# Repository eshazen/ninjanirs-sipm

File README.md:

# ninjanirs-sipm

Power supplies and electronics for SiPM-based optodes

Designs completed:

*  `KiCAD/lt3014-test` - test board with LT3014 voltage regulator
controlled by AD5270 digital pot, with INA201 current limiter
   * See [README](Testing/LT3014/README.md) for test details
* `KiCAD/sipm-hv-splitter` - candidate for in-system test
   * See [README](KiCAD/sipm-hv-splitter/README.md) for testing

Test logs:

* `Testing/LT3014` for the test board
* `Testing/sipm-splitter` for the splitter board

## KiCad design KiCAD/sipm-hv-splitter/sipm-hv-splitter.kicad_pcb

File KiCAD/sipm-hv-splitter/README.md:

# sipm-hv-splitter

## Description

This is a PCB intended to replace the "splitter" board, connecting
directly to a detector interface card with a very short ribbon.
It provides programmable, current-limited HV bias to 8 SiPMs along
with TIA readout of each SiPM.

The targent dimensions for the prototype are 2.5 x 1.3 inches.

The SiPM connectors are the "NIRX" standard .050" pitch 4-pin with
pinout as follows (top view of female header on this board):

| Function   | Number |   | Number | Function     |
|------------|--------|---|--------|--------------|
| V(BIAS)    | 2      |   | 1      | Signal       |
| Thermistor | 4      |   | 3      | GND (shield) |

The thermistor is optional and expected to be connected on only 1 of 8
SiPMs. 

The output connector to the readout adapter has the following pinout:

| Function | Number |   | Number | Function    |
|----------|--------|---|--------|-------------|
| V +12V   | 1      |   | 2      | V -20V      |
| GND      | 3      |   | 4      | Ch 7 signal |
| V +12V   | 5      |   | 6      | V -20V      |
| GND      | 7      |   | 8      | Ch 6 signal |
| V +12V   | 9      |   | 10     | V -20V      |
| GND      | 11     |   | 12     | Ch 6 signal |
| V +12V   | 13     |   | 14     | V -20V      |
| GND      | 15     |   | 16     | Ch 4 signal |
| V +12V   | 17     |   | 18     | V -20V      |
| GND      | 19     |   | 20     | Ch 3 signal |
| V +12V   | 21     |   | 22     | V -20V      |
| GND      | 23     |   | 24     | Ch 2 signal |
| V +12V   | 25     |   | 26     | V -20V      |
| GND      | 27     |   | 28     | Ch 1 signal |
| V +12V   | 29     |   | 30     | V -20V      |
| GND      | 31     |   | 32     | Ch 0 signal |
| COMM/RX  | 33     |   | 34     | COMM/RX     |

_NOTE:_ channel number order reversed to minimise crosstalk on the PCB.

`COMM/RX` is a logic signal (optionally containing UART prototcol
data) from the adapter card to the on-board MCU.  `COMM/TX` is an
optional half-duplex return path for bidirectional communication with
the adapter card.

## ECOs

* Cut track to SDO U5 pin 7 at chip.  Add 2.2k pull-up to 3.3V
on pin 7.
* Cut track to BOOST_ENA and wire to PD5 (pin 9) of U1.
* C39 wrong footprint on schematic/BOM (0201)

## Testing Log

### 11/11/26:

Summary:

Up to about 2.5mA is OK at 56V.  Firmware is updated
to provide more margin for failures.  Currently:

	DAC            195 (56V)
	ADC_VOLT_NOM   779 (55.8V) with range +/-10
	                    55.0 .. 56.6 more or less
    ADC_VOLT_LOW   472 (32V) at minimum VR output
	ADC_CURRENT_LOW 50 (1mA) at minimum VR output

Update board#1 firmware to current (tag `Splitter-FW-V1.1`).
<br>Modify the detector IF card I have bypass U13

--------------------------------------------------
Wire up a NIRx cable to alligator clip adapter.

Test with 47k load in parallel with 75k = 28.9k
<br>57/29.9 = 1.73mA

    > a
    56.8 V 1717.0 uA -104.0 degC
    >a 0
    83

ADJ on U4 is 1.2V

Try 10k (8.8k or 6.5mA).  Output is 62V on meter

    >a
    72.8 V 6723.2 uA -104.0 degC

<br>ADJ is 1.5V!
<br>IMON is ~ 1.1V
<br>Also 350mV 25kHz oscillation at end of NIRx cable.
<br>Pins on U2 (INA201):

    2 - 1.1
    3 - 0.287

    >a
    72.4 V 3599.5 uA -104.0 degC
    >a 0
    171
    >

Measure IMON @ 600mV.  (this is the trip point)

Back to 75k

    >a
    56.8 V 786.1 uA -104.0 degC
    >a 0
    39

Measure IMON @ 126mV.  

Test with 44k = 27.7k or 2mA.

    >a
    56.8 V 1841.1 uA -104.0 degC
    >a 0
    90
    >

With 22k bad news.  U4 VR output is 72V and ADJ=1.5V!

(realize that the SiPM Anode connection is not a good place
to connect my dummy load, so move to the shield (GND)).

Try again with 22k and see the same issue.
<br>44k is OK.
<br>32k (parallel with 75k so 22k) is OK.  Current = 2.5mA.

    >a
    56.8 V 2234.1 uA -104.0 degC
    >a 0
    108

Measure voltages:

    55.6 at testpoint (boost out)
    53.9 at end of cable.  
	
1k series gives a 1.8V drop so that's consistent	

### 11/10/26:

Board#2 is in the hands of Srikanth.  Seems to work OK but trips with
4 optodes exposed to room light.

Preparing Board#1 for shipment to NIRx.  Power up as-is with 12V.
LED D3 comes on briefly, then off.  D2 (trip) then on steady.
If the ISP is connected, D3 blinks fast.

Wire up 75k load on a NIRx cable and connect to optode #1.
Now get trip and fast blink.  Re-flash with debug software.

Power-up sequence:

    >p 170
	>vs 0
	>b 1
    >a
    56.9 V 765.4 uA -104.0 degC
	>a 0
    39

This seems reasonable.  57V / 75k = 760uA.

Recalculate trip point.  INA201 amp gain 50V/V
<br>Comparator VREF = 0.6V
<br>With R2=210k and R3=75k trip at IMON = 2.28V
<br>(2.28V/50)/3 = 15mA

Readback:  IMON = current * 3 Ohms * 50
<br>So 760uA * 3 * 50 = 114mV or 35 ADC counts.

### 2/26/26:

Thinking some more about the observed issues.  On the splitter the delta-v on
the LT3014 output is around 50mV, while on the test board with the MOSFET
load circuit it's more like 20mV.  50mv/57V * 1.2V = 1.1mV on the ADJ pin.
It seems not unlikely that ground bounce or capacitative coupling into the
ADJ pin could cause this.

Interesting... there is a C installed at C15 (soft start).  Try removing it.
Much better.

### 2/3/26:

Change feedback C on ch1 TIA from 1nf to 100pF.
<br>Oscillation gone!

Work plan after chat with BZ:

* Try various FB C's to make sure we're in a good range
* Change all FB C's on working board
* Test for measurable x-talk during 1.25ms pulse on neighboring channel
   * Shift in baseline
   * Change in Vbias
* Test with more SiPMs

<br>Change ch 2 FB to 470pF.  No oscillation.
<br>Change ch 1 FB back to 1000pF.  Yes oscillation (sanity check)
<br>Change ch 1-4 FB to 470pF.

### 2/2/26:

Power-up sequence:

    >p 170
	>vs 0
	>b 1

Should read 57V or so.  Note dummy load needed to avoid trip.

Testing S13360-3025PE.  3x3mm 25um pitch.  Vover = 5V, VBR 53+/-5
<br>Confirm that VBR is about 53.

   S13360-3025PE (gain 7e5)
   pot = 195.  V is 56V, 170uA+/-50uA
   100Hz pulse 100us wide 3.2V into red LED
   Output about 420mV.
   
Printing another box for a 2nd SiPM.

   S13360-3050PE (gain 1.7e6)
   Output about 3.95V
   
Gain should be about 2.5X higher.

__Oscillation:__ See 50MHz sine wave ~ 20mV pk-pk output of amp.
<br>With only open NIRX cable (60cm) we see a square-ish wave almost 100mV pk-pk.

The amp has a low-pass filter with ~10kHz cutoff.
<br>Try 100pF in parallel with the 1nF feedback cap.  If anything, worse.

### 1/22/26:

See below 8/7/25 for power hookups

Test board `OUT0` is pin 4 of ribbon, so SIG_0 which comes from pins 29-32 of Optodes header

Boost converter producing 73V but output always tripped.  Need dummy load?
<br>Make a optode cable with 100k.  Now it works!

The current readback seems wrong, though.  57/100k = 560uA
<br>The readout says 72.6uA

ADC is reading 31.  Sense resistor is 3.00 ohms.  So the raw current signal
should be 1.7mV across R9.  For the INA201 the gain is supposedly 50V/V
so 84mV for 560uA.  The expected ADC reading would be 26.  Observe 31-35
using raw `a 0` so maybe not so bad?

In `sipm_io.h` constant `NA_PER_ADC` is 2200.  Hmm.
Change to 20687.

### 9/30/25:

Testing board#2

* Power-up and flash OK.
* Boost output 73V
* VR range 31.2-60.8

* Change R17 to 2.7M to increase max voltage to 67V

Now the VR goes up to 65.2.

The current readback is jumping around from 8-20uA though.

Re-flash board#1 with avr-debug

Current readback similarly jumps around

### 9/17/25:

(all below board#1)

Finally have correct (hope) ribbon between test board and adapter.
Going to install firmware on the purple test board.

Currently it has:

```
hazen@hazen-botlab CIRCUITPY $ ls -l
total 6
-rw-r--r-- 1 hazen hazen  103 Dec 31  2019 boot_out.txt
-rw-r--r-- 1 hazen hazen 1608 Dec 18  2022 code.py
-rw-r--r-- 1 hazen hazen 2671 Dec 19  2022 DetAdapterTB.py
drwxr-xr-x 2 hazen hazen  512 Dec 31  2019 lib
```

(lib is empty).  Copying the following from BZ's ZIP:

```
-rw-rw-rw- 1 hazen hazen     889 Aug 28 00:51 code.py
-rw-rw-rw- 1 hazen hazen    8512 Aug 28 00:47 NN22DetectorAdapterTestBoard.py
-rw-rw-rw- 1 hazen hazen    3982 Oct 17  2024 TestFunctions.py
```

It works!  SiPM output voltage reported by python on the test board
varies with LED current.

### 9/12/25:

Working towards readout with BZ's red and purple boards.

TODO:

* Install R63, remove R62 on red board.  This disables the on-board LED and repurposes `A_COMM` as an
enable for the HV.  _Done_ (100 ohms for R63)
* Make firmware which powers up the HV and displays status
on the HV board LED.

### 9/11/25:

* Change R13 to 180k to up boost output to 75V.
* Change R17 to 2.7M to increase max voltage to 67V

Confirm with VOM we get 66.5V max output or so.

### 8/27/25:

Looking to use [test board](https://github.com/eshazen/ninjanirs-optode/tree/main/KiCAD/test-board) as a breakout.

```
  +6.5V  -  use for +12V power
  GND    -  ground
  -20V   -  use for -20V for TIA negative power
```

Solder wires to J1 pins 33 (comm TX) and 34 (comm RX).

### 8/20/25:

Load resistor of 66k on outputs.  Script `ramp_plot.py` makes
a nice set of V, I curvs vs DAC setting.

Ripple with scope probe ~ 20mV pk-pk.  100MHz always present,
20Hz (!) only when boost converter on.

Install parts for detector 0:

```
   R44, C47  (1k, 0.1uF) bias filter
   C23, C31 (0.1uF) bypass
   R28 (15k, TI)
   U13 (opa)
   R36 (15 ohms) output
   C39 (1n) feedback
```

### 8/4/25:

Issues with oscillation on output; seems like the LT3014.
Change C11 and C12 to 1uF 100V (vs 0.1uF).  Seems better.
Still some issues with startup.

Change R3 from 140k to 75k (double the overcurrent).
Now all seems good except for some ripple at max output.
Change R13 from 180k to 160k to up boost output to 65V.

All good so far.

### 7/29/25:

Add 2.2k pull-up on Digi Pot SDO.  It works!
<br>Move `BOOST_ENA` to PD5

Install U4, R17, R20 and C11, C12 as 0.1uF 100V.

### 7/28/25:

Started a new board, installed MCU and digi pot.

Found that ISP is unreliable here too.  Cut "SDO" track from digipot.
Now it seems to work reliably.  But Digi pot doesn't work.

Notice that the data sheet says that a pull-up is *required* on SDO
even if not used.

### 7/24/25:

Found a "feature" of the AVR SPI bus:  The pin called nSS (PB2)
must be driven high for the SPI bus to work.  We're using this
for BOOST_ENA so this is a bit of a problem.

More seriously, the ISP interface on the AVR seems to be dead.
This could be because we were using the ISP in 5V mode :(
<br>One can set 3.3V (host power) mode by removing the little yellow jumper
on the USBTinyISP.

May need to solder up a new board :( :(
<br>Start on board#2.  Install only 3.3V digital and MCU.
Programs fine.  Stopping for the weekend.

### 7/23/25:

Soldered 3.3V regulators, MCU and boost converter parts.
Soldered temporary FTDI serial thing on R1 site.

Boost converter works!  Outputting 61.3V, drawing 69mA on 12V.
Controlled as expected by `BOOST_ENA` output from MCU.

Install Digi pot.  Doesn't work :(  <br>
Verified SCK, MOSI, nSYNC all look OK. <br>
Nothing comes out MISO, POT stuck at 50%. <br>

Giving up for today

## Revision log

### 7/7/25:
Final checks

* Add LC filter on AVCC on MCU
* Add filter C on AREF
   * working on layout changes

### 7/3/25:  
First complete draft, posted to Basecamp

### Edits due from BZ on 7/1/25:

* Mis-wired RC filter on TIA input; should be on each SiPM bias line.
<br>_NOTE:_ the RC filter should be moved to the heirarchial block for
each channel for common layout? *DONE*
* Swap UART TX/RX *DONE*
* Use same symbol for all caps C2, C3 etc *DONE*
* Add filter on `THERM` *DONE*

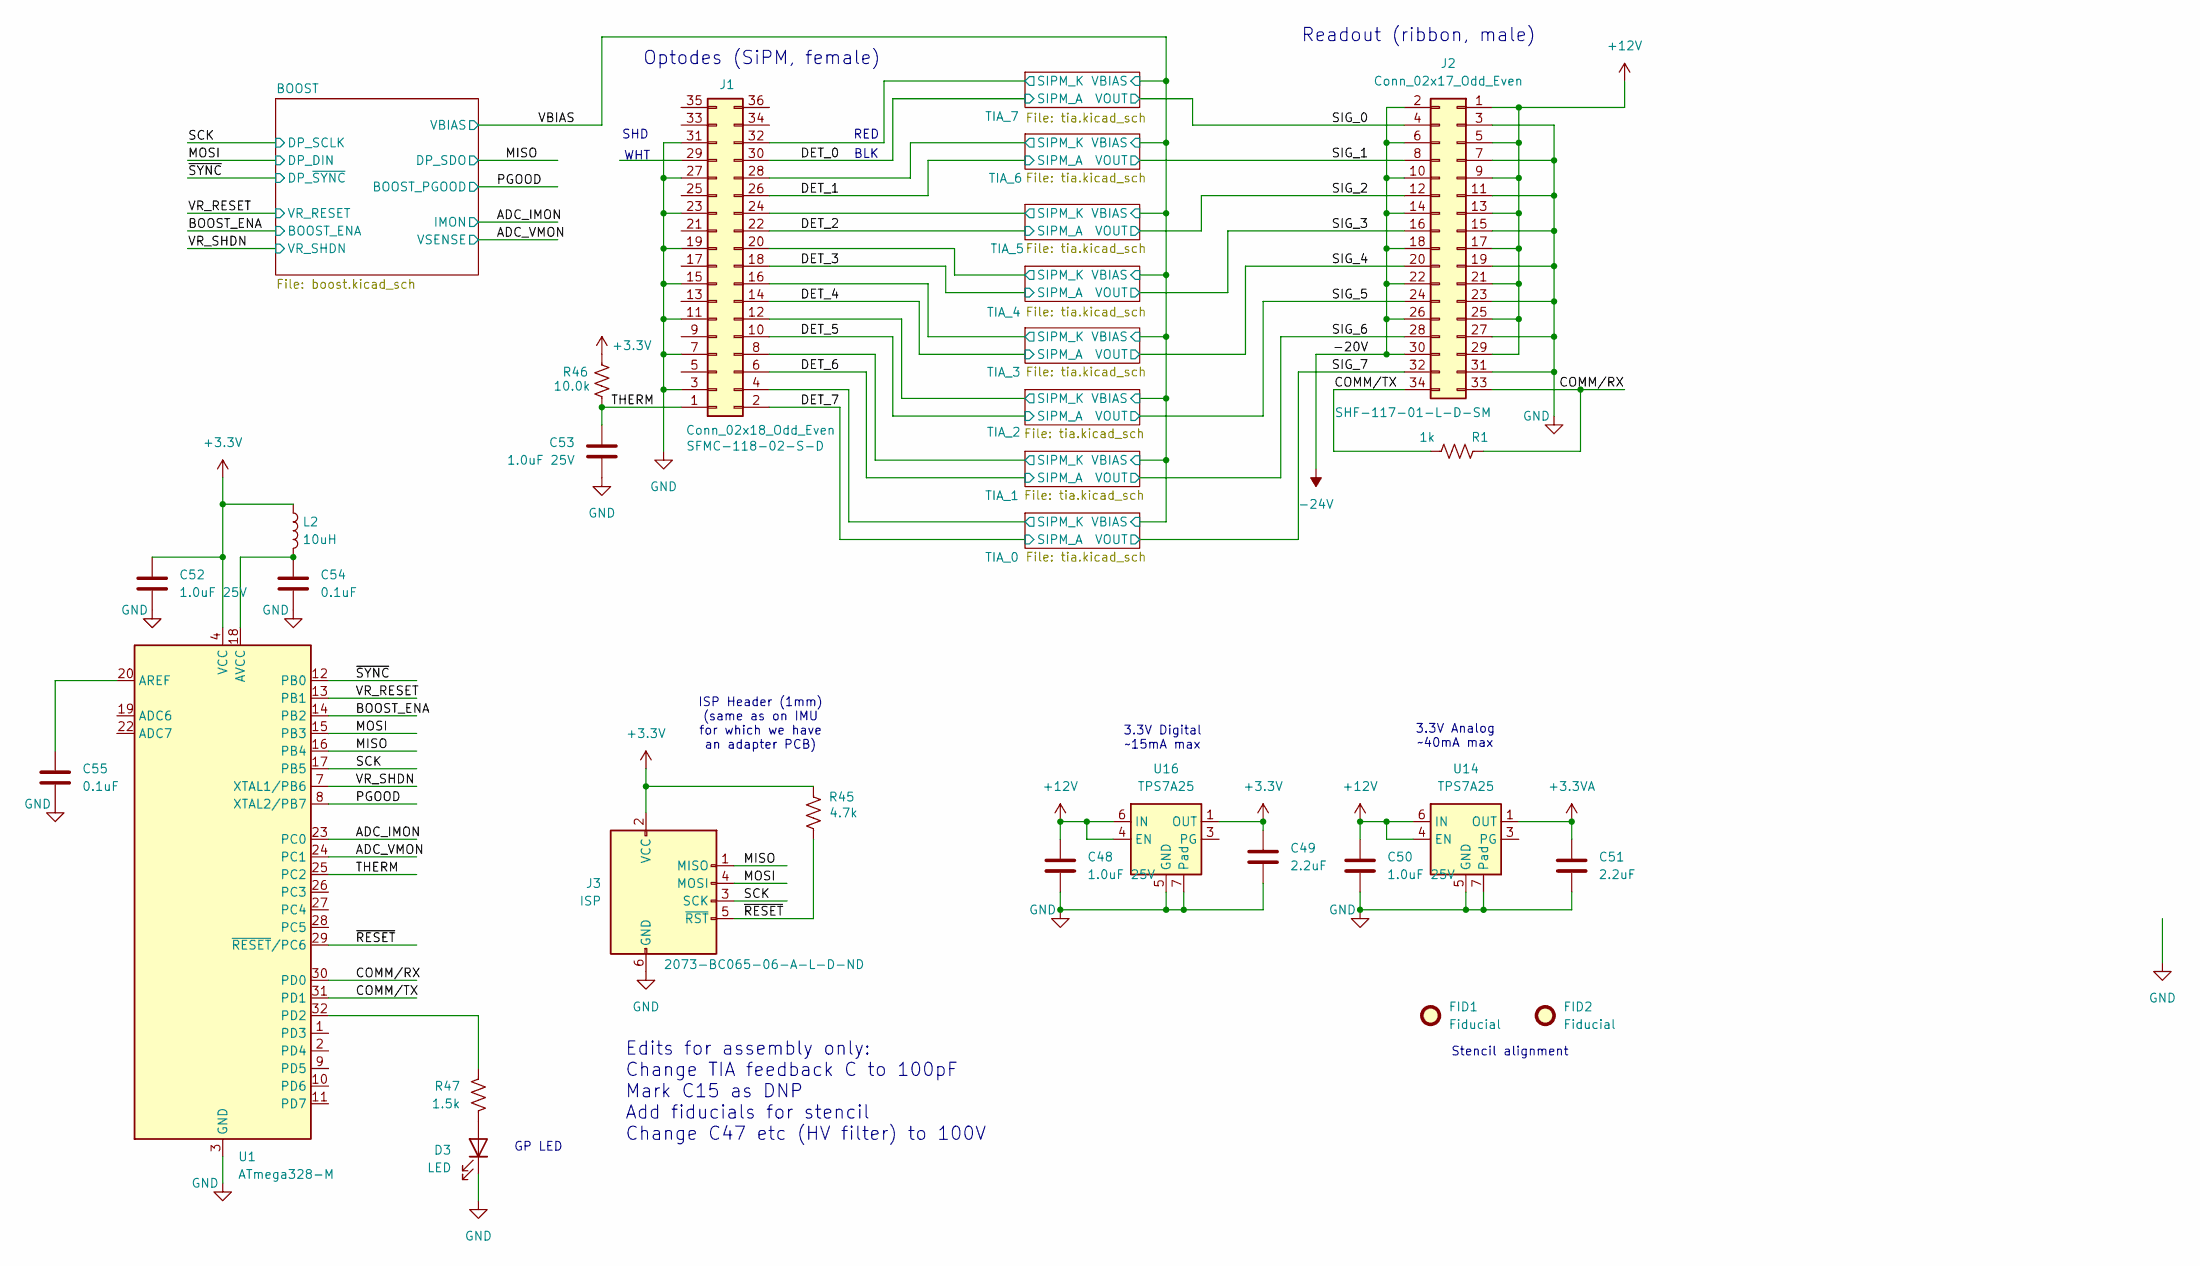
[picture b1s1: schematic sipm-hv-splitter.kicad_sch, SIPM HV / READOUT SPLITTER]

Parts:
C48, C50, C52, C53: 1.0uF 25V; C_0603_1608Metric_Pad1.08x0.95mm_HandSolder
C49, C51: 2.2uF; C_0603_1608Metric_Pad1.08x0.95mm_HandSolder
C54, C55: 0.1uF; C_0603_1608Metric_Pad1.08x0.95mm_HandSolder
D3: LED; my_SMT_0603
FID1, FID2: Fiducial; stencil_align_125
J1: Conn_02x18_Odd_Even; SAMTEC_SFMC-118-02-L-D
J2: Conn_02x17_Odd_Even; SHF-117-01-X-D-SM
J3: ISP; PinHeader_1x06_P1.00mm_Vertical
L2: 10uH; L_0603_1608Metric_Pad1.05x0.95mm_HandSolder
R1: 1k; R_0603_1608Metric_Pad0.98x0.95mm_HandSolder
R45: 4.7k; R_0603_1608Metric_Pad0.98x0.95mm_HandSolder
R46: 10.0k; R_0603_1608Metric_Pad0.98x0.95mm_HandSolder
R47: 1.5k; R_0603_1608Metric_Pad0.98x0.95mm_HandSolder
U1: ATmega328-M; QFN-32-1EP_5x5mm_P0.5mm_EP3.1x3.1mm
U14, U16: TPS7A25; WSON-6-1EP_2x2mm_P0.65mm_EP1x1.6mm_ThermalVias

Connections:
+3.3V: C49.1, C52.1, J3.2 (VCC), L2.1, R45.2, R46.2, U1.4 (VCC), U1.6 (VCC), U16.1 (OUT); also elsewhere on the board
+3.3VA: C51.1, U14.1 (OUT); also elsewhere on the board
+12V: C48.1, C50.1, J2.1, J2.5, J2.9, J2.13, J2.17, J2.21, J2.25, J2.29, U14.4 (EN), U14.6 (IN), U16.4 (EN), U16.6 (IN); also elsewhere on the board
-24V: J2.2, J2.6, J2.10, J2.14, J2.18, J2.22, J2.26, J2.30; also elsewhere on the board
/ADC_IMON: U1.23 (PC0); also elsewhere on the board
/ADC_VMON: U1.24 (PC1); also elsewhere on the board
/BOOST_ENA: U1.14 (PB2); also elsewhere on the board
/COMM/RX: J2.33, R1.1, U1.30 (PD0)
/COMM/TX: J2.34, R1.2, U1.31 (PD1)
/DET_0: J1.30; also elsewhere on the board
/DET_1: J1.26; also elsewhere on the board
/DET_2: J1.22; also elsewhere on the board
/DET_3: J1.18; also elsewhere on the board
/DET_4: J1.14; also elsewhere on the board
/DET_5: J1.10; also elsewhere on the board
/DET_6: J1.6; also elsewhere on the board
/DET_7: J1.2; also elsewhere on the board
/MISO: J3.1 (MISO), U1.16 (PB4); also elsewhere on the board
/MOSI: J3.4 (MOSI), U1.15 (PB3); also elsewhere on the board
/PGOOD: U1.8 (XTAL2/PB7); also elsewhere on the board
/SCK: J3.3 (SCK), U1.17 (PB5); also elsewhere on the board
/SIG_0: J2.4; also elsewhere on the board
/SIG_1: J2.8; also elsewhere on the board
/SIG_2: J2.12; also elsewhere on the board
/SIG_3: J2.16; also elsewhere on the board
/SIG_4: J2.20; also elsewhere on the board
/SIG_5: J2.24; also elsewhere on the board
/SIG_6: J2.28; also elsewhere on the board
/SIG_7: J2.32; also elsewhere on the board
/THERM: C53.1, J1.1, R46.1, U1.25 (PC2)
/TIA_0/SIPM_K: J1.4; also elsewhere on the board
/TIA_1/SIPM_K: J1.8; also elsewhere on the board
/TIA_2/SIPM_K: J1.12; also elsewhere on the board
/TIA_3/SIPM_K: J1.16; also elsewhere on the board
/TIA_4/SIPM_K: J1.20; also elsewhere on the board
/TIA_5/SIPM_K: J1.24; also elsewhere on the board
/TIA_6/SIPM_K: J1.28; also elsewhere on the board
/TIA_7/SIPM_K: J1.32; also elsewhere on the board
/VR_RESET: U1.13 (PB1); also elsewhere on the board
/VR_SHDN: U1.7 (XTAL1/PB6); also elsewhere on the board
/~RESET: J3.5 (~RST), R45.1, U1.29 (~RESET/PC6)
/~SYNC: U1.12 (PB0); also elsewhere on the board
GND: C48.2, C49.2, C50.2, C51.2, C52.2, C53.2, C54.2, C55.2, D3.1 (K), J1.3, J1.7, J1.11, J1.15, J1.19, J1.23, J1.27, J1.31, J2.3, J2.7, J2.11, J2.15, J2.19, J2.23, J2.27, J2.31, J3.6 (GND), U1.3 (GND), U1.5 (GND), U1.21 (GND), U1.33 (GND), U14.5 (GND), U14.7 (Pad), U16.5 (GND), U16.7 (Pad); also elsewhere on the board
unnamed: D3.2 (A), R47.2
unnamed: C55.1, U1.20 (AREF)
unnamed: C54.1, L2.2, U1.18 (AVCC)
unnamed: R47.1, U1.32 (PD2)

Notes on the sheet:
GP LED
3.3V Digital ~15mA max
WHT
RED
BLK
Stencil alignment
Optodes (SiPM, female)
Edits for assembly only: Change TIA feedback C to 100pF Mark C15 as DNP Add fiducials for stencil Change C47 etc (HV filter) to 100V
3.3V Analog ~40mA max
SHD
ISP Header (1mm) (same as on IMU for which we have an adapter PCB)
Readout (ribbon, male)

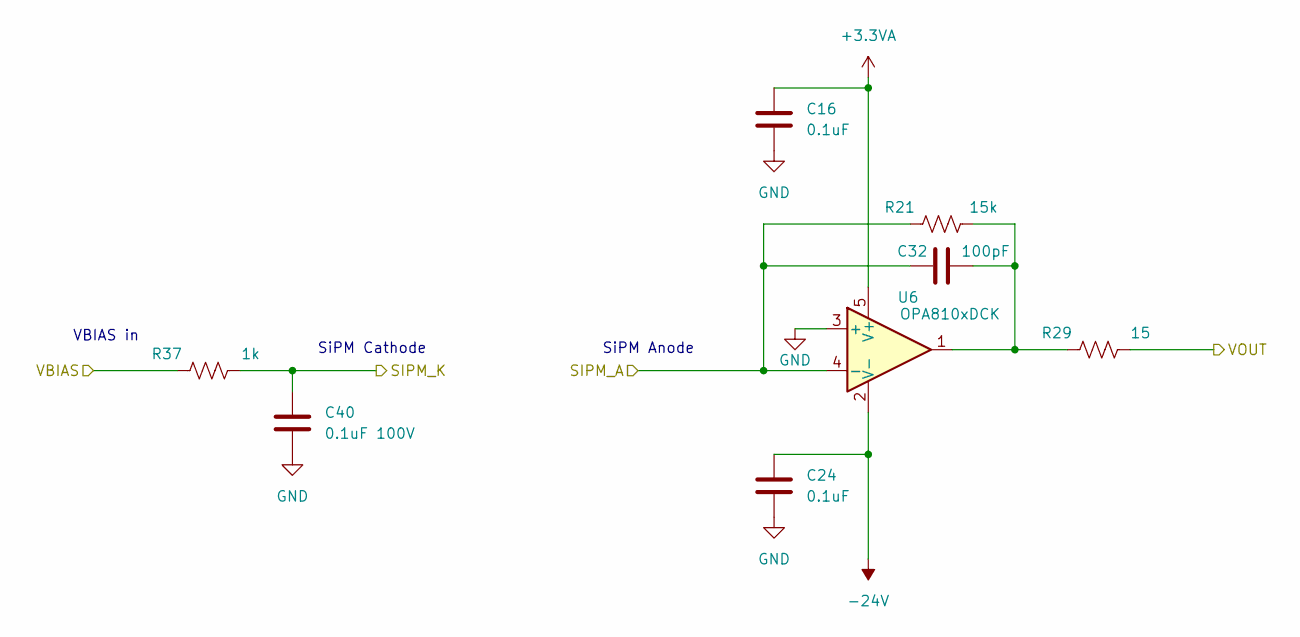
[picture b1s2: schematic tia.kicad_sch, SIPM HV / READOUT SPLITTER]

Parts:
C16, C24: 0.1uF; C_0603_1608Metric_Pad1.08x0.95mm_HandSolder
C32: 100pF; C_0603_1608Metric_Pad1.08x0.95mm_HandSolder
C40: 0.1uF 100V; C_0603_1608Metric_Pad1.08x0.95mm_HandSolder
R21: 15k; R_0603_1608Metric_Pad0.98x0.95mm_HandSolder
R29: 15; R_0603_1608Metric_Pad0.98x0.95mm_HandSolder
R37: 1k; R_0603_1608Metric_Pad0.98x0.95mm_HandSolder
U6: OPA810xDCK; Texas_R-PDSO-G5_DCK-5

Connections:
+3.3VA: C16.1, U6.5 (V+); also elsewhere on the board
-24V: C24.1, U6.2 (V-); also elsewhere on the board
/DET_7: C32.1, R21.1, U6.4 (-); also elsewhere on the board
/SIG_7: R29.2; also elsewhere on the board
/TIA_0/SIPM_K: C40.1, R37.2; also elsewhere on the board
/VBIAS: R37.1; also elsewhere on the board
GND: C16.2, C24.2, C40.2, U6.3 (+); also elsewhere on the board
unnamed: C32.2, R21.2, R29.1, U6.1

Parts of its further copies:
C17, C18, C19, C20, C21, C22, C23, C25, C26, C27, C28, C29, C30, C31: 0.1uF; C_0603_1608Metric_Pad1.08x0.95mm_HandSolder
R22, R23, R24, R25, R26, R27, R28: 15k; R_0603_1608Metric_Pad0.98x0.95mm_HandSolder
R30, R31, R32, R33, R34, R35, R36: 15; R_0603_1608Metric_Pad0.98x0.95mm_HandSolder
R38, R39, R40, R41, R42, R43, R44: 1k; R_0603_1608Metric_Pad0.98x0.95mm_HandSolder
U7, U8, U9, U10, U11, U12, U13: OPA810xDCK; Texas_R-PDSO-G5_DCK-5

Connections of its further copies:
+3.3VA: C17.1, C18.1, C19.1, C20.1, C21.1, C22.1, C23.1, U7.5 (V+), U8.5 (V+), U9.5 (V+), U10.5 (V+), U11.5 (V+), U12.5 (V+), U13.5 (V+); also elsewhere on the board
-24V: C25.1, C26.1, C27.1, C28.1, C29.1, C30.1, C31.1, U7.2 (V-), U8.2 (V-), U9.2 (V-), U10.2 (V-), U11.2 (V-), U12.2 (V-), U13.2 (V-); also elsewhere on the board
/DET_0: R28.1, U13.4 (-); also elsewhere on the board
/DET_1: R27.1, U12.4 (-); also elsewhere on the board
/DET_2: R26.1, U11.4 (-); also elsewhere on the board
/DET_3: R25.1, U10.4 (-); also elsewhere on the board
/DET_4: R24.1, U9.4 (-); also elsewhere on the board
/DET_5: R23.1, U8.4 (-); also elsewhere on the board
/DET_6: R22.1, U7.4 (-); also elsewhere on the board
/SIG_0: R36.2; also elsewhere on the board
/SIG_1: R35.2; also elsewhere on the board
/SIG_2: R34.2; also elsewhere on the board
/SIG_3: R33.2; also elsewhere on the board
/SIG_4: R32.2; also elsewhere on the board
/SIG_5: R31.2; also elsewhere on the board
/SIG_6: R30.2; also elsewhere on the board
/TIA_1/SIPM_K: R38.2; also elsewhere on the board
/TIA_2/SIPM_K: R39.2; also elsewhere on the board
/TIA_3/SIPM_K: R40.2; also elsewhere on the board
/TIA_4/SIPM_K: R41.2; also elsewhere on the board
/TIA_5/SIPM_K: R42.2; also elsewhere on the board
/TIA_6/SIPM_K: R43.2; also elsewhere on the board
/TIA_7/SIPM_K: R44.2; also elsewhere on the board
/VBIAS: R38.1, R39.1, R40.1, R41.1, R42.1, R43.1, R44.1; also elsewhere on the board
GND: C17.2, C18.2, C19.2, C20.2, C21.2, C22.2, C23.2, C25.2, C26.2, C27.2, C28.2, C29.2, C30.2, C31.2, U7.3 (+), U8.3 (+), U9.3 (+), U10.3 (+), U11.3 (+), U12.3 (+), U13.3 (+); also elsewhere on the board
unnamed 49: R22.2, R30.1, U7.1; also elsewhere on the board
unnamed 50: R23.2, R31.1, U8.1; also elsewhere on the board
unnamed 51: R24.2, R32.1, U9.1; also elsewhere on the board
unnamed 52: R25.2, R33.1, U10.1; also elsewhere on the board
unnamed 53: R26.2, R34.1, U11.1; also elsewhere on the board
unnamed 54: R27.2, R35.1, U12.1; also elsewhere on the board
unnamed 55: R28.2, R36.1, U13.1; also elsewhere on the board

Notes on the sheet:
SiPM Anode
VBIAS in
SiPM Cathode

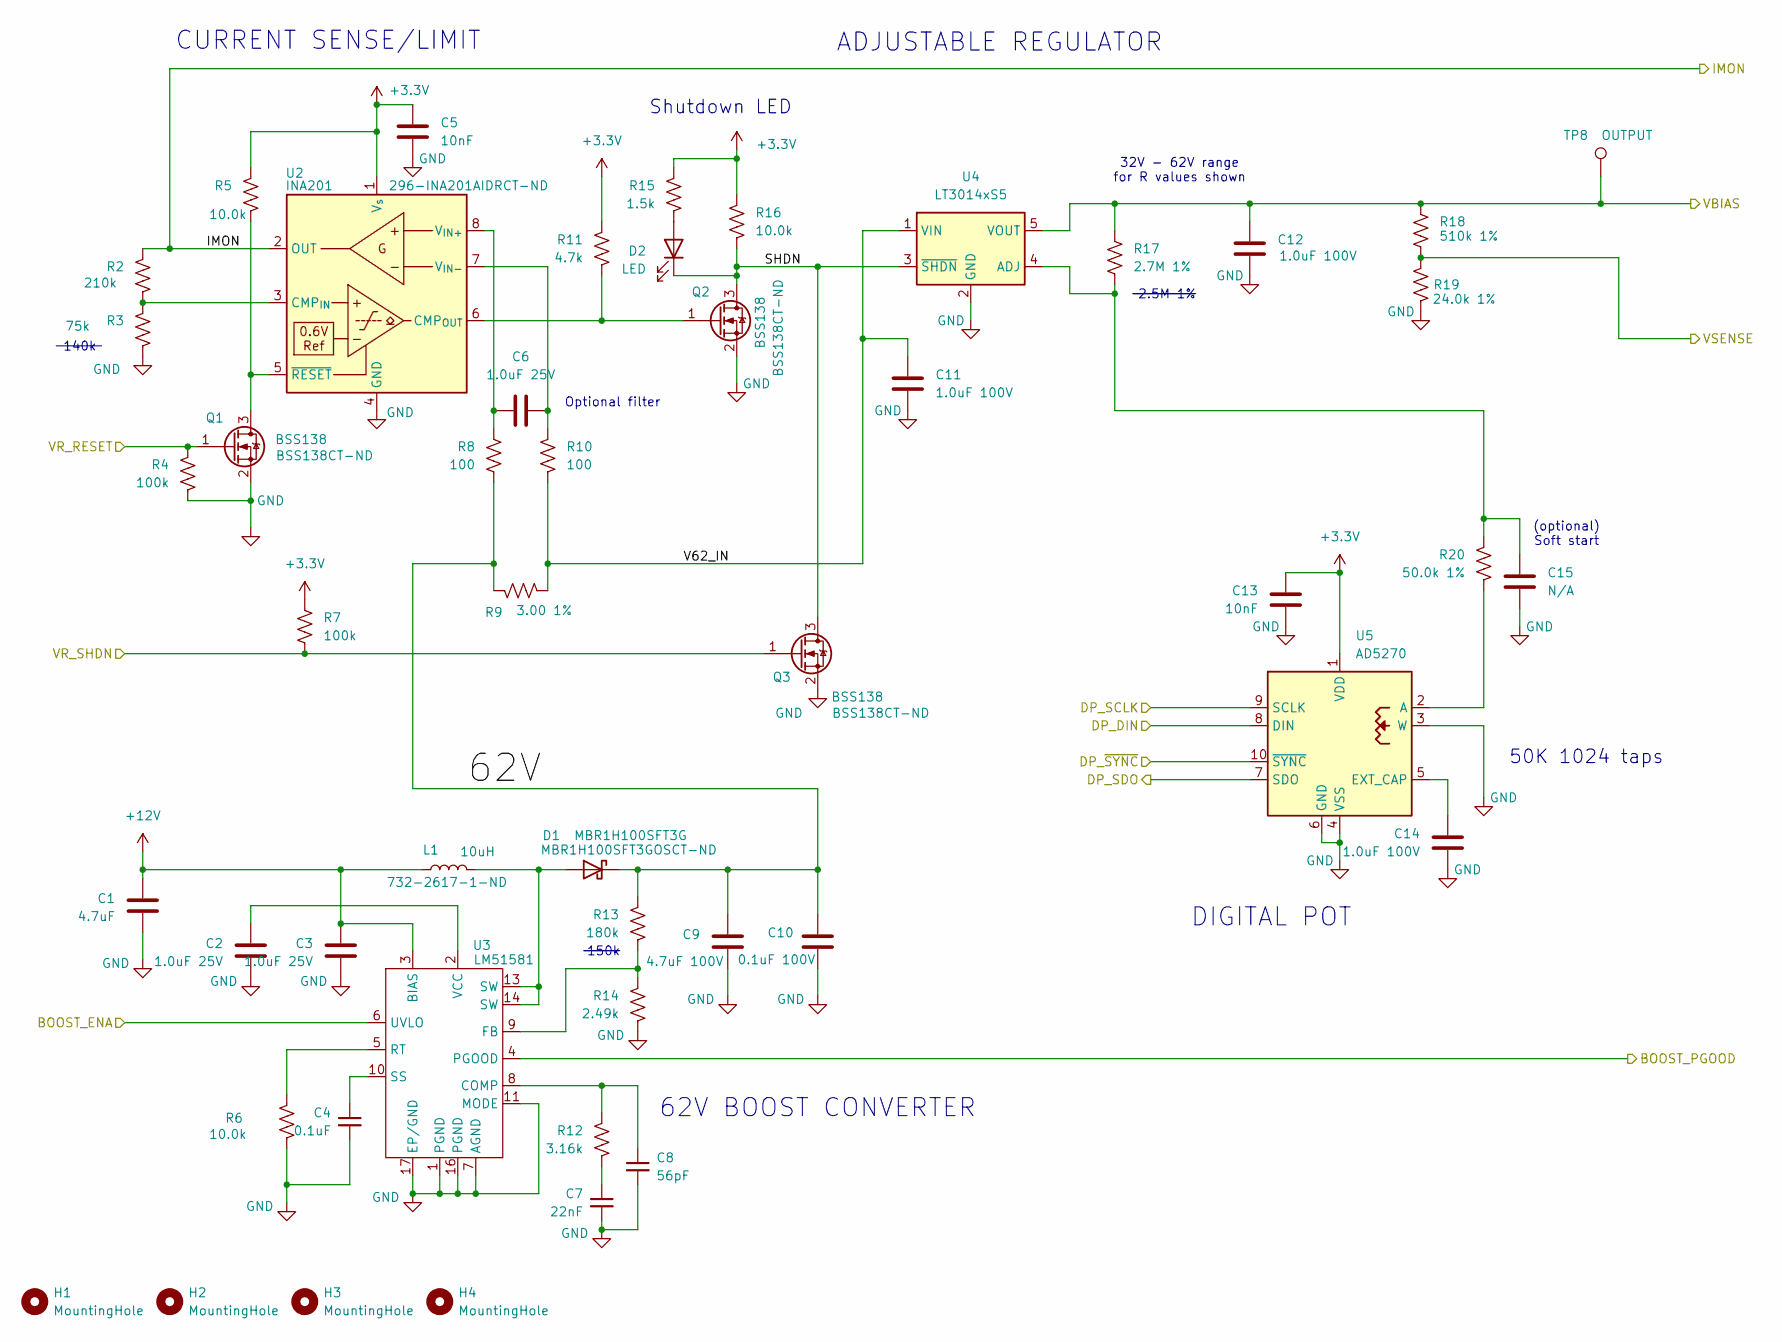
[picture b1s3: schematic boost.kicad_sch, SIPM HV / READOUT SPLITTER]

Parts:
C1: 4.7uF; C_0603_1608Metric_Pad1.08x0.95mm_HandSolder
C2, C3, C6: 1.0uF 25V; C_0603_1608Metric_Pad1.08x0.95mm_HandSolder
C4: 0.1uF; C_0603_1608Metric_Pad1.08x0.95mm_HandSolder
C5, C13: 10nF; C_0603_1608Metric_Pad1.08x0.95mm_HandSolder
C7: 22nF; C_0603_1608Metric_Pad1.08x0.95mm_HandSolder
C8: 56pF; C_0603_1608Metric_Pad1.08x0.95mm_HandSolder
C9: 4.7uF 100V; C_1206_3216Metric_Pad1.33x1.80mm_HandSolder
C10: 0.1uF 100V; C_0603_1608Metric_Pad1.08x0.95mm_HandSolder
C11, C12, C14: 1.0uF 100V; C_0603_1608Metric_Pad1.08x0.95mm_HandSolder
C15: N/A; C_0603_1608Metric_Pad1.08x0.95mm_HandSolder
D1: MBR1H100SFT3G; Nexperia_CFP3_SOD-123W
D2: LED; my_SMT_0603
H1, H2, H3, H4: MountingHole; MountingHole_2.2mm_M2
L1: 10uH; WE-TPC-ind
Q1, Q2, Q3: BSS138; SOT-23
R2: 210k; R_0603_1608Metric_Pad0.98x0.95mm_HandSolder
R3: 75k; R_0603_1608Metric_Pad0.98x0.95mm_HandSolder
R4, R7: 100k; R_0603_1608Metric_Pad0.98x0.95mm_HandSolder
R5, R6, R16: 10.0k; R_0603_1608Metric_Pad0.98x0.95mm_HandSolder
R8, R10: 100; R_0603_1608Metric_Pad0.98x0.95mm_HandSolder
R9: 3.00 1%; R_1206_3216Metric_Pad1.30x1.75mm_HandSolder
R11: 4.7k; R_0603_1608Metric_Pad0.98x0.95mm_HandSolder
R12: 3.16k; R_0603_1608Metric_Pad0.98x0.95mm_HandSolder
R13: 180k; R_0603_1608Metric_Pad0.98x0.95mm_HandSolder
R14: 2.49k; R_0603_1608Metric_Pad0.98x0.95mm_HandSolder
R15: 1.5k; R_0603_1608Metric_Pad0.98x0.95mm_HandSolder
R17: 2.7M 1%; R_0603_1608Metric_Pad0.98x0.95mm_HandSolder
R18: 510k 1%; R_0603_1608Metric_Pad0.98x0.95mm_HandSolder
R19: 24.0k 1%; R_0603_1608Metric_Pad0.98x0.95mm_HandSolder
R20: 50.0k 1%; R_0603_1608Metric_Pad0.98x0.95mm_HandSolder
TP8: OUTPUT; TestPoint_Pad_D1.0mm
U2: INA201; SOIC-8_3.9x4.9mm_P1.27mm
U3: LM51581; QFN-16_EP_3x3_Pitch0.5mm
U4: LT3014xS5; SOT-23-5
U5: AD5270; MSOP-10_3x3mm_P0.5mm

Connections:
+3.3V: C5.1, C13.1, R5.1, R7.1, R11.1, R15.1, R16.1, U2.1 (V_{s}), U5.1 (VDD); also elsewhere on the board
+12V: C1.1, C3.1, L1.1, U3.3 (BIAS); also elsewhere on the board
/ADC_IMON: R2.1, U2.2 (OUT); also elsewhere on the board
/ADC_VMON: R18.2, R19.1; also elsewhere on the board
/BOOST/62V: C9.1, C10.1, D1.1 (K), R8.2, R9.1, R13.1
/BOOST/SHDN: D2.1 (K), Q2.3 (D), Q3.3 (D), R16.2, U4.3 (~SHDN)
/BOOST/V62_IN: C11.1, R9.2, R10.2, U4.1 (VIN)
/BOOST_ENA: U3.6 (UVLO); also elsewhere on the board
/MISO: U5.7 (SDO); also elsewhere on the board
/MOSI: U5.8 (DIN); also elsewhere on the board
/PGOOD: U3.4 (PGOOD); also elsewhere on the board
/SCK: U5.9 (SCLK); also elsewhere on the board
/VBIAS: C12.1, R17.1, R18.1, TP8.1 (1_1), U4.5 (VOUT); also elsewhere on the board
/VR_RESET: Q1.1 (G), R4.1; also elsewhere on the board
/VR_SHDN: Q3.1 (G), R7.2; also elsewhere on the board
/~SYNC: U5.10 (~SYNC); also elsewhere on the board
GND: C1.2, C2.2, C3.2, C4.2, C5.2, C7.2, C8.2, C9.2, C10.2, C11.2, C12.2, C13.2, C14.2, C15.2, Q1.2 (S), Q2.2 (S), Q3.2 (S), R3.2, R4.2, R6.2, R14.2, R19.2, U2.4 (GND), U3.1 (PGND), U3.7 (AGND), U3.11 (MODE), U3.16 (PGND), U3.17 (EP/GND), U4.2 (GND), U5.3 (W), U5.4 (VSS), U5.6 (GND); also elsewhere on the board
unnamed: C7.1, R12.2
unnamed: D1.2 (A), L1.2, U3.13 (SW), U3.14 (SW)
unnamed: D2.2 (A), R15.2
unnamed: Q1.3 (D), R5.2, U2.5 (~RESET)
unnamed: Q2.1 (G), R11.2, U2.6 (CMP_{OUT})
unnamed: R2.2, R3.1, U2.3 (CMP_{IN})
unnamed: C6.1, R8.1, U2.8 (V_{IN+})
unnamed: C6.2, R10.1, U2.7 (V_{IN-})
unnamed: C8.1, R12.1, U3.8 (COMP)
unnamed: R13.2, R14.1, U3.9 (FB)
unnamed: R6.1, U3.5 (RT)
unnamed: C4.1, U3.10 (SS)
unnamed: C2.1, U3.2 (VCC)
unnamed: C15.1, R17.2, R20.1, U4.4 (ADJ)
unnamed: R20.2, U5.2 (A)
unnamed: C14.1, U5.5 (EXT_CAP)

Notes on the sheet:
CURRENT SENSE/LIMIT
50K 1024 taps
ADJUSTABLE REGULATOR
Shutdown LED
DIGITAL POT
32V - 62V range for R values shown
150k
62V BOOST CONVERTER
Optional filter
2.5M 1%
(optional) Soft start
140k

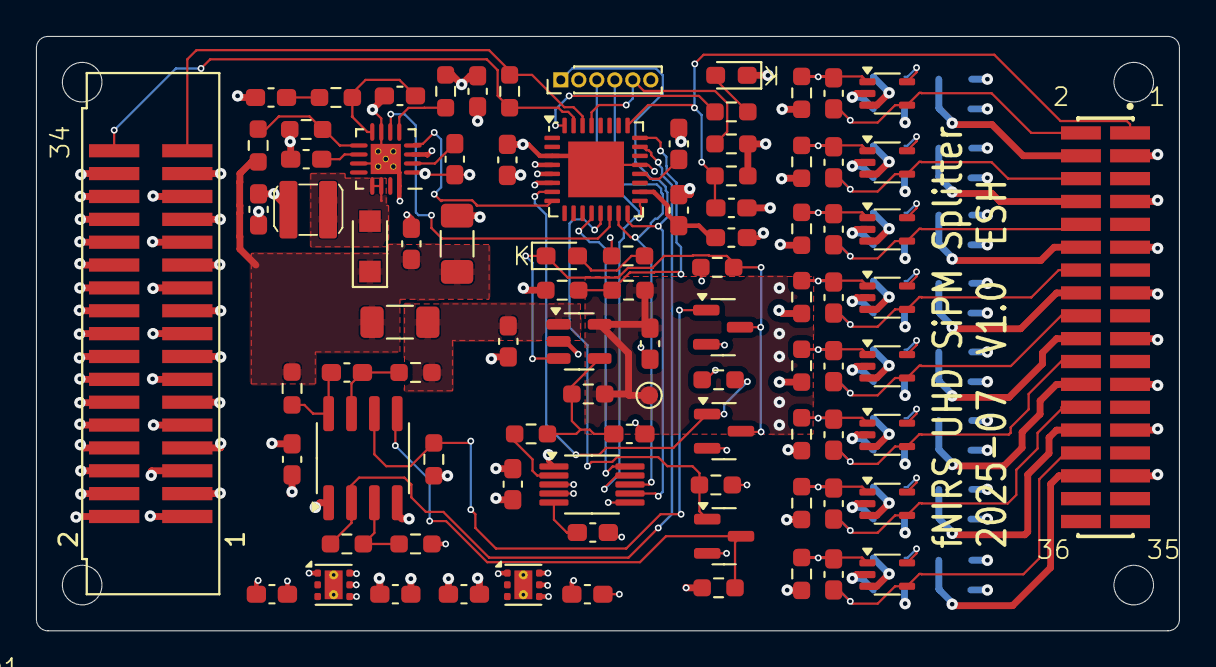
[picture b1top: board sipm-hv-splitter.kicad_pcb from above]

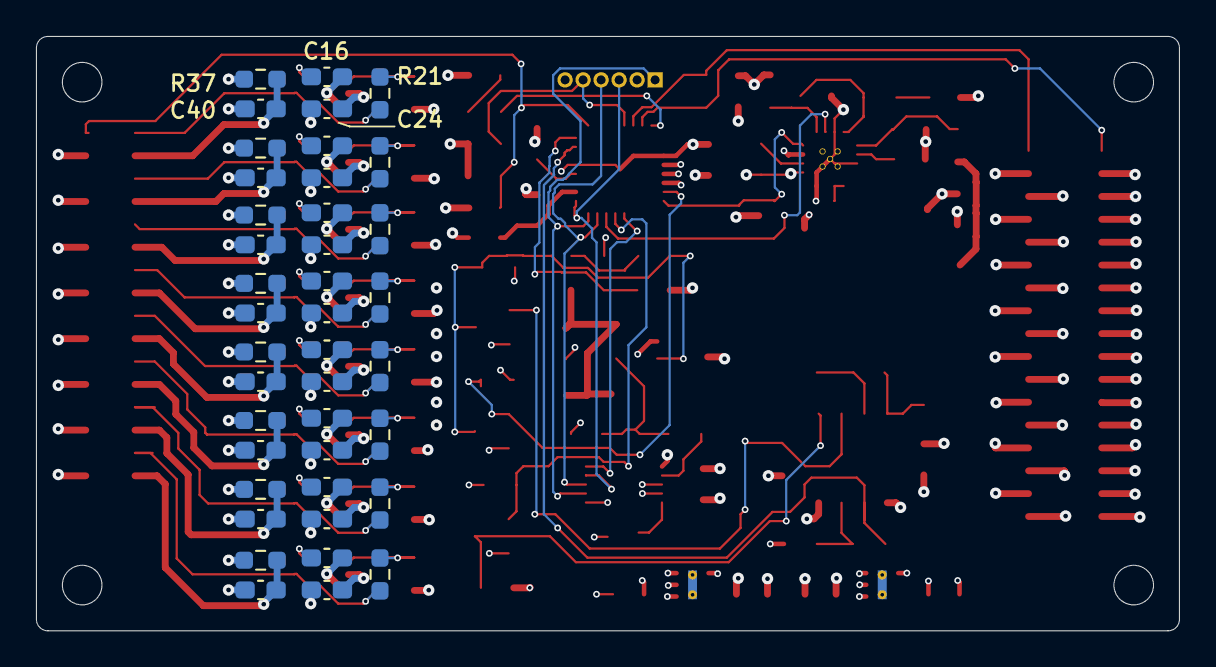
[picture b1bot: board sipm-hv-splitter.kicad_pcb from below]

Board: 6 copper layers, 63.5 x 33.0 mm, 135 parts (40 on the bottom side), 75 nets.

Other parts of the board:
C33, C34, C35, C36, C37, C38, C39: 1nF; C_0603_1608Metric_Pad1.08x0.95mm_HandSolder
C41, C42, C43, C44, C45, C46, C47: 0.1uF; C_0603_1608Metric_Pad1.08x0.95mm_HandSolder

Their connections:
/DET_0: C39.1; also elsewhere on the board
/DET_1: C38.1; also elsewhere on the board
/DET_2: C37.1; also elsewhere on the board
/DET_3: C36.1; also elsewhere on the board
/DET_4: C35.1; also elsewhere on the board
/DET_5: C34.1; also elsewhere on the board
/DET_6: C33.1; also elsewhere on the board
/TIA_1/SIPM_K: C41.1; also elsewhere on the board
/TIA_2/SIPM_K: C42.1; also elsewhere on the board
/TIA_3/SIPM_K: C43.1; also elsewhere on the board
/TIA_4/SIPM_K: C44.1; also elsewhere on the board
/TIA_5/SIPM_K: C45.1; also elsewhere on the board
/TIA_6/SIPM_K: C46.1; also elsewhere on the board
/TIA_7/SIPM_K: C47.1; also elsewhere on the board
GND: C41.2, C42.2, C43.2, C44.2, C45.2, C46.2, C47.2; also elsewhere on the board
unnamed 49: C33.2; also elsewhere on the board
unnamed 50: C34.2; also elsewhere on the board
unnamed 51: C35.2; also elsewhere on the board
unnamed 52: C36.2; also elsewhere on the board
unnamed 53: C37.2; also elsewhere on the board
unnamed 54: C38.2; also elsewhere on the board
unnamed 55: C39.2; also elsewhere on the board

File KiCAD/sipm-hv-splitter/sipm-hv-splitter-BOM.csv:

Build Qty:,3,,,,
,,,,,
Reference,Qty,Value,MfgNo,CatNo,OrderQty
C1,1,4.7uF,CL10A475KO8NNNC,1276-1784-1-ND,3
"C2,C3,C6,C48,C50,C52,C53",7,1.0uF,CL10B105KO8NNNC,1276-1019-1-ND,21
"C4,C16,C17,C18,C19,C20,C21,C22,C23,C24,C25,C26,C27,C28,C29,C30,C31,C40,C41,C42,C43,C44,C45,C46,C47,C54,C55",27,0.1uF,CC0603KRX7R7BB104,311-1088-1-ND,81
"C5,C13",2,10nF,06035C103MAZ2A,478-KGF15AR71H103MTCT-ND,6
C7,1,22nF,0603B223K160CT,1292-1415-1-ND,3
C8,1,56pF,600S560JT250XT4K,478-600S560JT250XT4KCT-ND,3
C9,1,4.7uF 100V,GRM31CC72A475KE11L,490-18620-1-ND,3
C10,1,0.1uF 100V,CL10B104KC8NNNC,1276-6807-1-ND,3
"C11,C12,C14",3,1.0uF 100V,GRM188D72A105ME01W,490-GRM188D72A105ME01WCT-ND,9
"C32,C33,C34,C35,C36,C37,C38,C39",8,1nF,CL03B102KOSVPNC,1276-CL03B102KOSVPNCCT-ND,24
"C49,C51",2,2.2uF,TMK107ABJ225KA-T,587-2909-1-ND,6
D1,1,MBR1H100SFT3G,MBR1H100SFT3G,MBR1H100SFT3GOSCT-ND,3
"D2,D3",2,LED,B19Y1USD-20C000113U1930,3147-B19Y1USD-20C000113U1930CT-ND,6
J1,1,Conn_02x18_Odd_Even,SFMC-118-02-S-D,SFMC-118-02-S-D-ND,3
J2,1,Conn_02x17_Odd_Even,SHF-117-01-L-D-SM,SAM9921-ND,3
J3,1,ISP,BC065-06-A-L-D,2073-BC065-06-A-L-D-ND,3
L1,1,10uH,744025100,732-2617-1-ND,3
L2,1,10uH,MLZ1608N100LT000,445-6755-1-ND,3
"Q1,Q2,Q3",3,BSS138,BSS138,BSS138CT-ND,9
"R1,R37,R38,R39,R40,R41,R42,R43,R44",9,1k,RMCF0603FT1K00,RMCF0603FT1K00CT-ND,27
R2,1,210k,RC0603FR-07210KL,311-210KHRCT-ND,3
R3,1,140k,RC0603FR-07140KL,311-140KHRCT-ND,3
R4,1,100k,RC0603FR-07100KL,311-100KHRCT-ND,3
"R5,R6,R16,R46",4,10.0k,"CRCW0603100KFKEA,RC0603FR-0710KL",311-10.0KHRCT-ND,12
R7,1,100k,CRCW0603100KFKEA,541-100KHCT-ND,3
"R8,R10",2,100,ERJ-3EKF1000V,P100HCT-ND,6
R9,1,3.00 1%,MFCR1206F3R00QHR,4506-MFCR1206F3R00QHRCT-ND,3
R11,1,4.7k,RT0603BRD074K7L,YAG1676CT-ND,3
R12,1,3.16k,CRCW06033K16FKEAC,541-5389-1-ND,3
R13,1,150k,ERJ-3EKF1503V,P150KHCT-ND,3
R14,1,2.49k,CRCW06032K49FKEAC,541-4044-1-ND,3
"R15,R47",2,1.5k,RT0603BRD071K5L,YAG1570CT-ND,6
R17,1,2.50M 1%,RMCF0603FT2M49,RMCF0603FT2M49CT-ND,3
R18,1,510k 1%,RMCF0603FT510K,RMCF0603FT510KCT-ND,3
R19,1,24.0k 1%,RMCF0603FT24K0,RMCF0603FT24K0CT-ND,3
R20,1,50.0k 1%,RT0603BRD0750KL,13-RT0603BRD0750KLCT-ND,3
"R21,R22,R23,R24,R25,R26,R27,R28",8,15k,CRG0603F15K,A121558CT-ND,24
"R29,R30,R31,R32,R33,R34,R35,R36",8,15,RC0603FR-0715RL,311-15.0HRCT-ND,24
R45,1,4.7k,ERJ-3EKF4701V,P4.70KHCT-ND,3
U1,1,ATmega328-M,ATMEGA328P-MU,ATMEGA328P-MU-ND,3
U2,1,INA201,INA201AIDR,296-INA201AIDRCT-ND,3
U3,1,LM51581,LM51581RTER,296-LM51581RTERCT-ND,3
U4,1,LT3014xS5,LT3014ES5#TRPBF,LT3014ES5#TRPBFCT-ND,3
U5,1,AD5270,AD5270BRMZ-50,505-AD5270BRMZ-50-ND,3
"U6,U7,U8,U9,U10,U11,U12,U13",8,OPA810xDCK,OPA810IDCKR,296-OPA810IDCKRCT-ND,24
"U14,U16",2,TPS7A25,TPS7A2533DRVR,296-TPS7A2533DRVRCT-ND,6

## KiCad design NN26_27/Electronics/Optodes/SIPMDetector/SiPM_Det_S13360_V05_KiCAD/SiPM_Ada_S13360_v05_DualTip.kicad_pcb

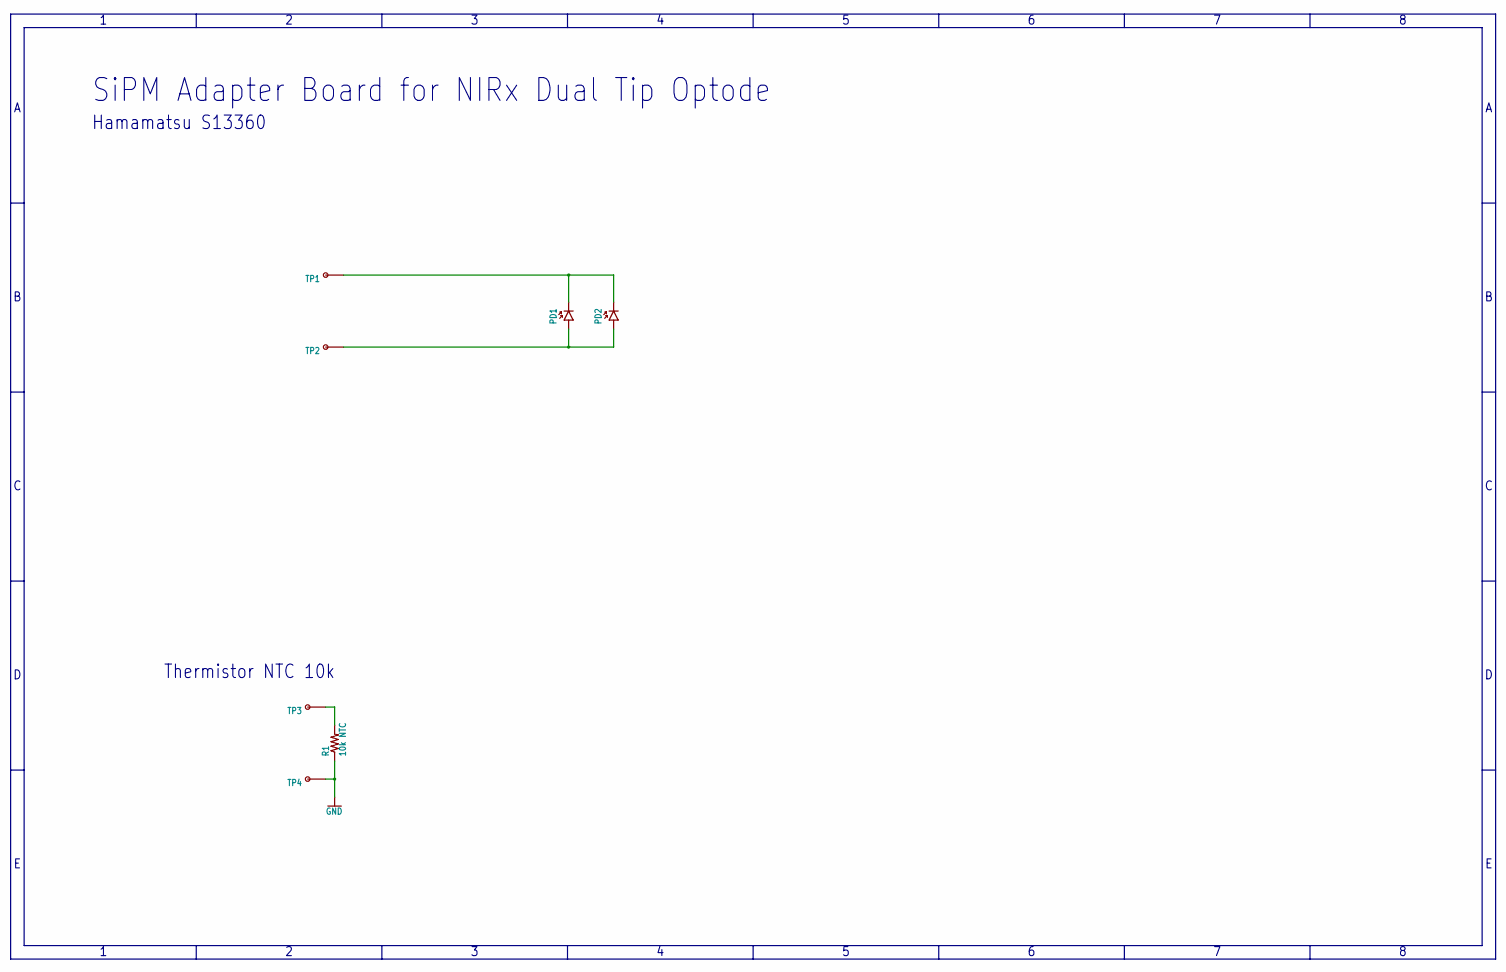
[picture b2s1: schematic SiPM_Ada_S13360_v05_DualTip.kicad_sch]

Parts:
PD1, PD2: PHOTODIODE_S13360-30XXPE; S13360-30XXPE
R1: 10k NTC; 0603-RES
TP1, TP2, TP3, TP4: TESTPOINT_PADMEDIUM; TESTPAD_MEDIUM

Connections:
A: PD1.A, PD2.A, TP2.P$1
C: PD1.C, PD2.C, TP1.P$1
GND: R1.1, TP4.P$1
T: R1.2, TP3.P$1

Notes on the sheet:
Thermistor NTC 10k
SiPM Adapter Board for NIRx Dual Tip Optode
Hamamatsu S13360

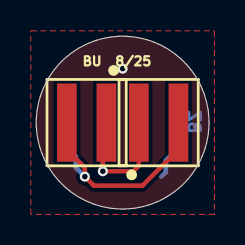
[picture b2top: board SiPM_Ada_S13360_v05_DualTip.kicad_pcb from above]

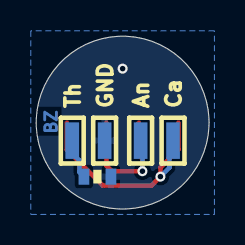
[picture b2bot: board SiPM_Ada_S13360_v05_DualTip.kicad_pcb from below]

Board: 2 copper layers, 9.6 x 9.6 mm, 7 parts (5 on the bottom side), 4 nets.

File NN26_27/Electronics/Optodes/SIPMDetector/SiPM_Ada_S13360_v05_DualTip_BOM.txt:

PD1, PD2: Hamamatsu S13360-3050PE
R1: NTCG163JF103FT1
TP1, TP2, TP3, TP4: DNP (wire solder pads)
